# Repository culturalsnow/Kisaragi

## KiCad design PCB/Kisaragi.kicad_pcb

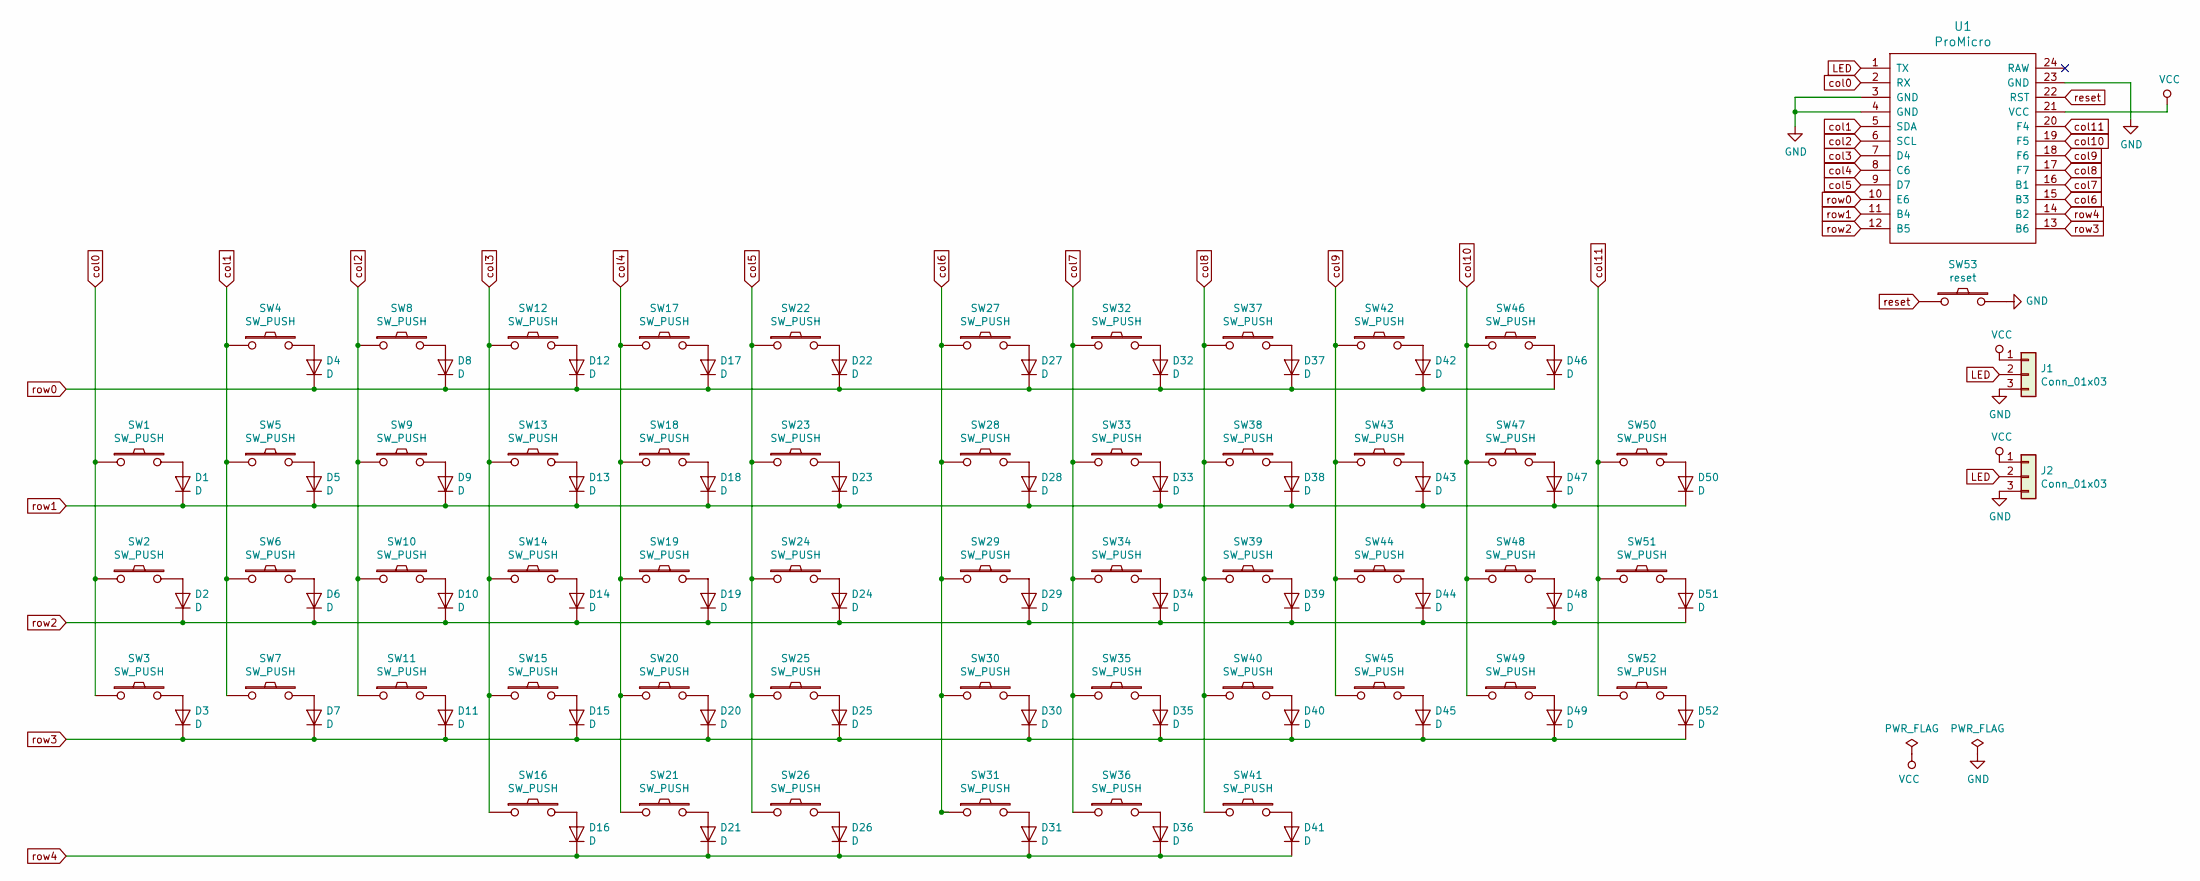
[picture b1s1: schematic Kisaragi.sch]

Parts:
D1, D2, D3, D4, D5, D6, D7, D8, D9, D10, D11, D12, D13, D14, D15, D16, D17, D18, D19, D20, D21, D22, D23, D24, D25, D26, D27, D28, D29, D30, D31, D32, D33, D34, D35, D36, D37, D38, D39, D40, D41, D42, D43, D44, D45, D46, D47, D48, D49, D50, D51, D52: D; D_SOD-123
J1, J2: Conn_01x03; LEDStrip
SW1, SW2, SW3, SW4, SW5, SW6, SW7, SW8, SW9, SW10, SW11, SW12, SW13, SW14, SW15, SW16, SW17, SW18, SW19, SW20, SW21, SW22, SW23, SW24, SW25, SW26, SW27, SW28, SW29, SW30, SW31, SW32, SW33, SW34, SW35, SW36, SW37, SW38, SW39, SW40, SW41, SW42, SW43, SW44, SW45, SW46, SW47, SW48, SW49, SW50, SW51, SW52: SW_PUSH; MX_Plate_100H
SW53: reset; ResetSW
U1: ProMicro; ProMicro_v2_Backside

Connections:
GND: J1.3, J2.3, SW53.2, U1.3 (GND), U1.4 (GND), U1.23 (GND)
LED: J1.2, J2.2, U1.1 (TX)
unnamed: D1.2 (A), SW1.2
unnamed: D2.2 (A), SW2.2
unnamed: D3.2 (A), SW3.2
unnamed: D4.2 (A), SW4.2
unnamed: D5.2 (A), SW5.2
unnamed: D6.2 (A), SW6.2
unnamed: D7.2 (A), SW7.2
unnamed: D8.2 (A), SW8.2
unnamed: D9.2 (A), SW9.2
unnamed: D10.2 (A), SW10.2
unnamed: D11.2 (A), SW11.2
unnamed: D12.2 (A), SW12.2
unnamed: D13.2 (A), SW13.2
unnamed: D14.2 (A), SW14.2
unnamed: D15.2 (A), SW15.2
unnamed: D16.2 (A), SW16.2
unnamed: D17.2 (A), SW17.2
unnamed: D18.2 (A), SW18.2
unnamed: D19.2 (A), SW19.2
unnamed: D20.2 (A), SW20.2
unnamed: D21.2 (A), SW21.2
unnamed: D22.2 (A), SW22.2
unnamed: D23.2 (A), SW23.2
unnamed: D24.2 (A), SW24.2
unnamed: D25.2 (A), SW25.2
unnamed: D26.2 (A), SW26.2
unnamed: D27.2 (A), SW27.2
unnamed: D28.2 (A), SW28.2
unnamed: D29.2 (A), SW29.2
unnamed: D30.2 (A), SW30.2
unnamed: D31.2 (A), SW31.2
unnamed: D32.2 (A), SW32.2
unnamed: D33.2 (A), SW33.2
unnamed: D34.2 (A), SW34.2
unnamed: D35.2 (A), SW35.2
unnamed: D36.2 (A), SW36.2
unnamed: D37.2 (A), SW37.2
unnamed: D38.2 (A), SW38.2
unnamed: D39.2 (A), SW39.2
unnamed: D40.2 (A), SW40.2
unnamed: D41.2 (A), SW41.2
unnamed: D42.2 (A), SW42.2
unnamed: D43.2 (A), SW43.2
unnamed: D44.2 (A), SW44.2
unnamed: D45.2 (A), SW45.2
unnamed: D46.2 (A), SW46.2
unnamed: D47.2 (A), SW47.2
unnamed: D48.2 (A), SW48.2
unnamed: D49.2 (A), SW49.2
unnamed: D50.2 (A), SW50.2
unnamed: D51.2 (A), SW51.2
unnamed: D52.2 (A), SW52.2
VCC: J1.1, J2.1, U1.21 (VCC)
col0: SW1.1, SW2.1, SW3.1, U1.2 (RX)
col1: SW4.1, SW5.1, SW6.1, SW7.1, U1.5 (SDA)
col2: SW8.1, SW9.1, SW10.1, SW11.1, U1.6 (SCL)
col3: SW12.1, SW13.1, SW14.1, SW15.1, SW16.1, U1.7 (D4)
col4: SW17.1, SW18.1, SW19.1, SW20.1, SW21.1, U1.8 (C6)
col5: SW22.1, SW23.1, SW24.1, SW25.1, SW26.1, U1.9 (D7)
col6: SW27.1, SW28.1, SW29.1, SW30.1, SW31.1, U1.15 (B3)
col7: SW32.1, SW33.1, SW34.1, SW35.1, SW36.1, U1.16 (B1)
col8: SW37.1, SW38.1, SW39.1, SW40.1, SW41.1, U1.17 (F7)
col9: SW42.1, SW43.1, SW44.1, SW45.1, U1.18 (F6)
col10: SW46.1, SW47.1, SW48.1, SW49.1, U1.19 (F5)
col11: SW50.1, SW51.1, SW52.1, U1.20 (F4)
reset: SW53.1, U1.22 (RST)
row0: D4.1 (K), D8.1 (K), D12.1 (K), D17.1 (K), D22.1 (K), D27.1 (K), D32.1 (K), D37.1 (K), D42.1 (K), D46.1 (K), U1.10 (E6)
row1: D1.1 (K), D5.1 (K), D9.1 (K), D13.1 (K), D18.1 (K), D23.1 (K), D28.1 (K), D33.1 (K), D38.1 (K), D43.1 (K), D47.1 (K), D50.1 (K), U1.11 (B4)
row2: D2.1 (K), D6.1 (K), D10.1 (K), D14.1 (K), D19.1 (K), D24.1 (K), D29.1 (K), D34.1 (K), D39.1 (K), D44.1 (K), D48.1 (K), D51.1 (K), U1.12 (B5)
row3: D3.1 (K), D7.1 (K), D11.1 (K), D15.1 (K), D20.1 (K), D25.1 (K), D30.1 (K), D35.1 (K), D40.1 (K), D45.1 (K), D49.1 (K), D52.1 (K), U1.13 (B6)
row4: D16.1 (K), D21.1 (K), D26.1 (K), D31.1 (K), D36.1 (K), D41.1 (K), U1.14 (B2)

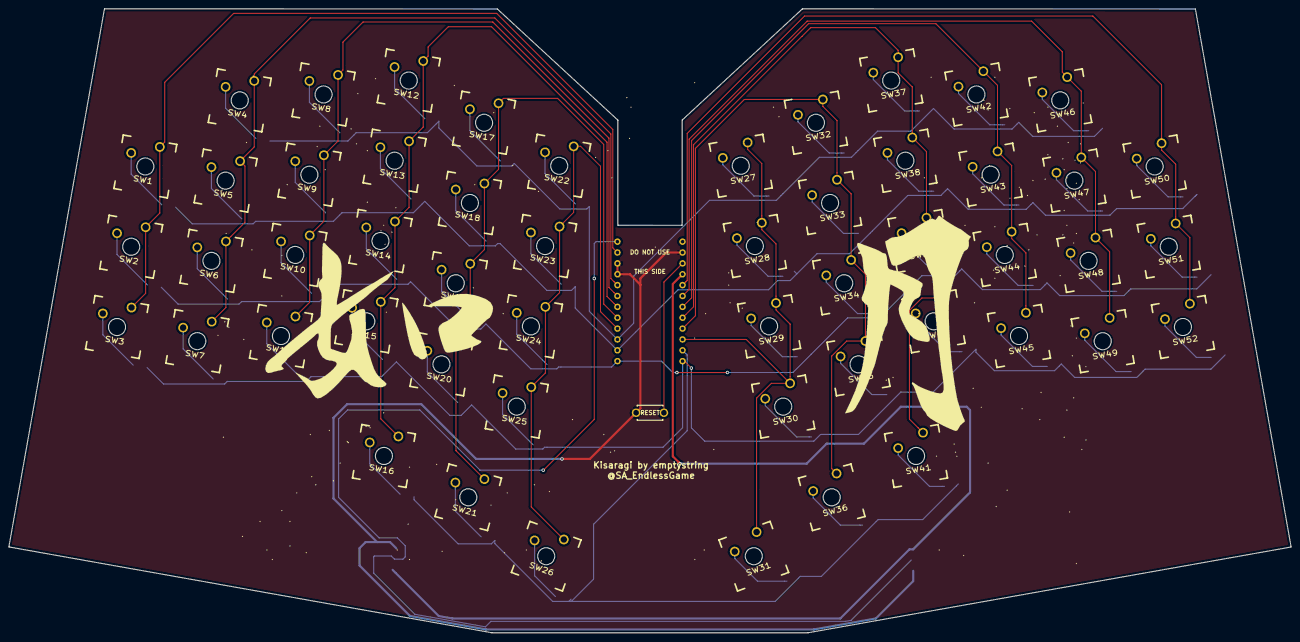
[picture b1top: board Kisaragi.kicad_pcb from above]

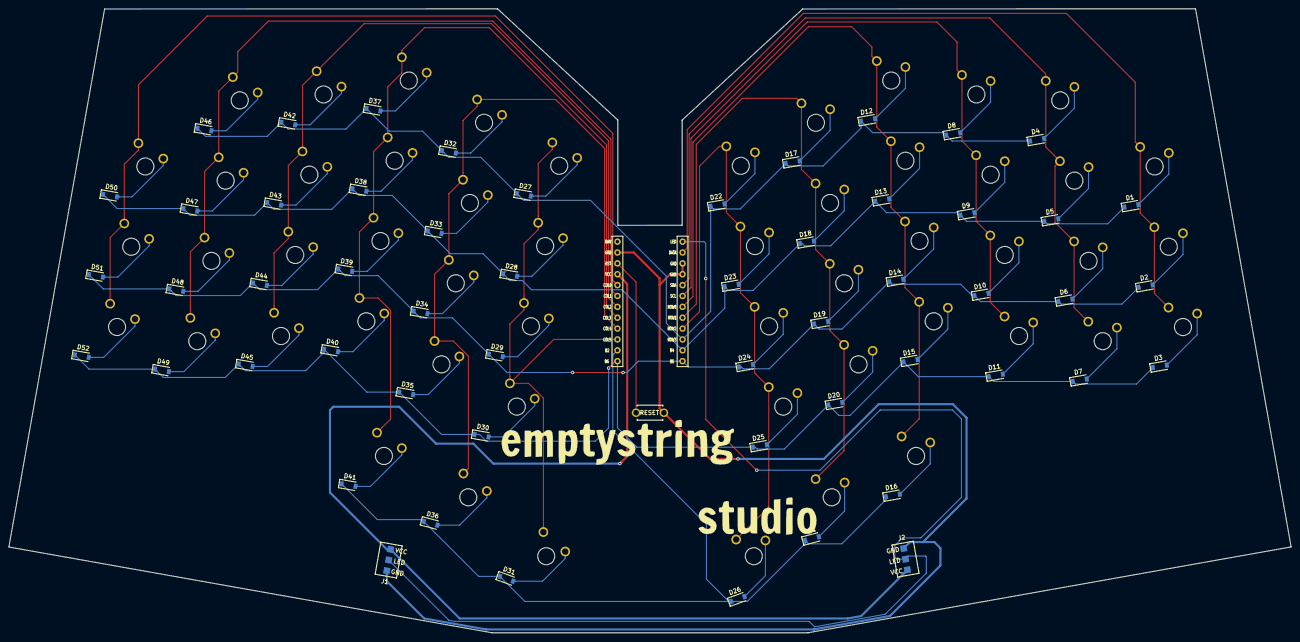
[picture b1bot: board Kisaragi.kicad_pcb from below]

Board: 2 copper layers, 299.7 x 145.8 mm, 108 parts (55 on the bottom side), 73 nets.

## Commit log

2019-02-24 added logos
2019-02-24 ignore ds_store
2019-02-25 added LED strip support
